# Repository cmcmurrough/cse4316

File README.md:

CSE 4316: Senior Design
========

Repository containing files related to CSE senior design

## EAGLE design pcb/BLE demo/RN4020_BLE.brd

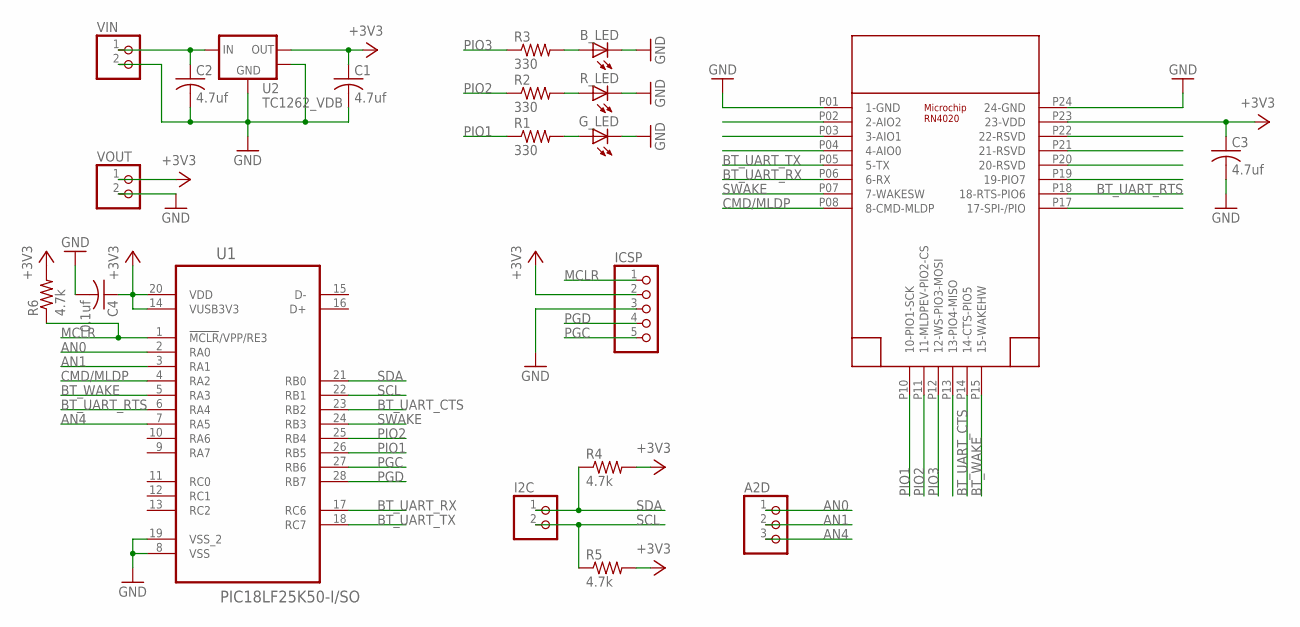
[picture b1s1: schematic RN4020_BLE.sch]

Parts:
A2D: PINHD-1X3; 1X03
B_LED: LEDSMT1206; 1206
C1, C2, C3: 4.7uf; C1206
C4: 0.1uf; C1206
G_LED: LEDSMT1206; 1206
I2C: PINHD-1X2; 1X02
ICSP: PINHD-1X5; 1X05
R1, R2, R3: 330; R1206
R4, R5, R6: 4.7k; R1206
R_LED: LEDSMT1206; 1206
U1: PIC18LF25K50-I/SO; SOIC127P1032X265-28N
U2: TC1262_VDB; SOT-223-3
U$1: RN4020; RN4020SMD
VIN: PINHD-1X2; 1X02
VOUT: PINHD-1X2; 1X02

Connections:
+3V3: C1.1, C3.1, C4.1, ICSP.2, R4.2, R5.2, R6.2, U1.14 (VUSB3V3), U1.20 (VDD), U2.3 (VOUT), U$1.P23 (23-VDD), VOUT.1
AN0: A2D.1, U1.2 (RA0)
AN1: A2D.2, U1.3 (RA1)
AN4: A2D.3, U1.7 (RA5)
BT_UART_CTS: U1.23 (RB2), U$1.P14 (14-CTS-PIO5)
BT_UART_RTS: U1.6 (RA4), U$1.P18 (18-RTS-PIO6)
BT_UART_RX: U1.17 (RC6), U$1.P06 (6-RX)
BT_UART_TX: U1.18 (RC7), U$1.P05 (5-TX)
BT_WAKE: U1.5 (RA3), U$1.P15 (15-WAKEHW)
CMD/MLDP: U1.4 (RA2), U$1.P08 (8-CMD-MLDP)
GND: B_LED.C, C1.2, C2.2, C3.2, C4.2, G_LED.C, ICSP.3, R_LED.C, U1.8 (VSS), U1.19 (VSS_2), U2.2 (GND), U2.4 (TAB), U$1.P01 (1-GND), U$1.P24 (24-GND), VIN.2, VOUT.2
MCLR: ICSP.1, R6.1, U1.1 (!MCLR!/VPP/RE3)
unnamed: G_LED.A, R1.2
unnamed: R2.2, R_LED.A
unnamed: B_LED.A, R3.2
unnamed: C2.1, U2.1 (VIN), VIN.1
PGC: ICSP.5, U1.27 (RB6)
PGD: ICSP.4, U1.28 (RB7)
PIO1: R1.1, U1.26 (RB5), U$1.P10 (10-PIO1-SCK)
PIO2: R2.1, U1.25 (RB4), U$1.P11 (11-MLDPEV-PIO2-CS)
PIO3: R3.1, U$1.P12 (12-WS-PIO3-MOSI)
SCL: I2C.2, R5.1, U1.22 (RB1)
SDA: I2C.1, R4.1, U1.21 (RB0)
SWAKE: U1.24 (RB3), U$1.P07 (7-WAKESW)

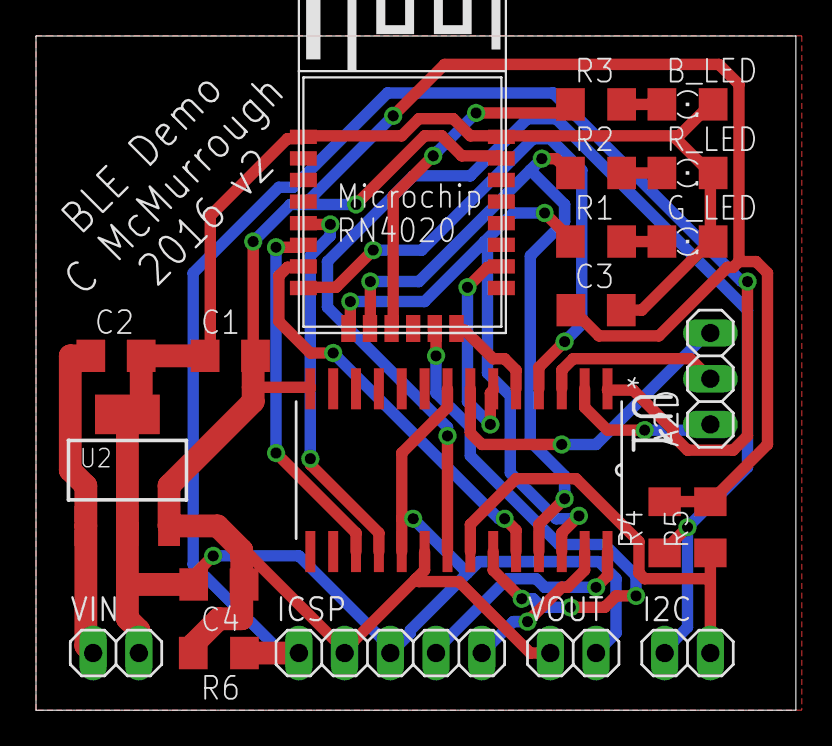
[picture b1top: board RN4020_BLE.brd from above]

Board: 2 copper layers, 42.2 x 37.5 mm, 21 parts (0 on the bottom side), 24 nets.

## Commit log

2019-01-14 initial checking (repository move)
2019-01-14 update to charter template
2019-11-11 added REST example
2019-11-12 update to REST example
2019-11-12 completed REST example
2019-12-01 added sparkfun artemis folder
2019-12-01 added Artemis BLE stepper demo
2019-12-02 added esp8266 access point server example
2020-01-02 update to requirements worksheet
2020-08-14 update to project charter
2020-09-30 update opencv
2020-10-21 typo fix
2020-12-18 update to individual statu reports
2020-12-19 update to individual status report template
2021-02-03 checkin of ML example
2021-02-03 minor tweak to ML script
2021-10-01 update to file structure and status report template
2021-10-19 added security requirements section
2022-02-07 added openlayers mapping example
2022-02-09 removed unused CSS
2022-09-26 Separated MLPClassifier into train/deploy modules. Minor bug fixes
2022-10-21 added lab storage card
2022-10-23 added RTK setup
2022-10-23 RTK update
2022-11-10 added drone 3D print parts
2022-11-19 restructure
2023-04-13 uploaded PLC example code
2023-09-20 added sprint presentation templates
2023-12-04 update to sprint report template
2024-02-26 relay toggle checkin
